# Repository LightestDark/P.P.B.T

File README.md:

# P.P.B.T

This project is a low-power smart keychain that combines E-paper display technology with NFC, designed to work with minimal energy and remain readable even when completely unpowered.

The system is split into two separate modules:

-E-Paper + NFC Keychain Board

Waveshare e paper display is used, following the websites recommended parts, using a crystal oscillator for graphics and a tiny flash memory for the images!
Used an NFC tag plugin for the coil for the NFC tag which calculates the impedance of the coil!

Added extra male pins for future endeavours if i want to add things to the board?

-Solar-Powered DC-DC Booster Board (external, detachable)

Follows a old schematic for an IKEA outdoor light, repurposed with smaller parts to make it cheaper, it uses a buckboost converter to get a steady flow from the solar panel to safely charge or power anything, in my case a strip of leds i will stick on the board case!

**This separation keeps the keychain compact, efficient, and flexible.**

**E PAPER + NFC SCHEMATIC/BOARD/MODEL:**

** SOLAR POWERED PSU **

The e-paper display shows text or graphics and keeps the image with zero power. Power is only needed when the display updates.
The NFC works passively, powered by the reader, allowing phones to scan the keychain even if the battery is empty.

To keep the main board simple and efficient, LED lighting is powered by a separate solar-powered DC-DC booster board. This board takes energy from a small solar panel and boosts it to drive LEDs around the keychain, without affecting the e-paper or NFC system.

CASE:

Pretty happy with the colour scheme and how it looks!

Main points of note:
PLA (probably)
Added tolerances for easy fitting since im hoping to use a friciton for the lid and the bottom
Added heat set insert holes
Added male header pin space for added functionality in the future
Added solar powered pcb on the underside, that will be wired to external solar panel and a led strip stuck onto the board
Added keychain hole onto the board (for coolness)

Underside:

Solar powered pcb on underside:

Under the hood:

Hopefully this is good enough to protect the board!

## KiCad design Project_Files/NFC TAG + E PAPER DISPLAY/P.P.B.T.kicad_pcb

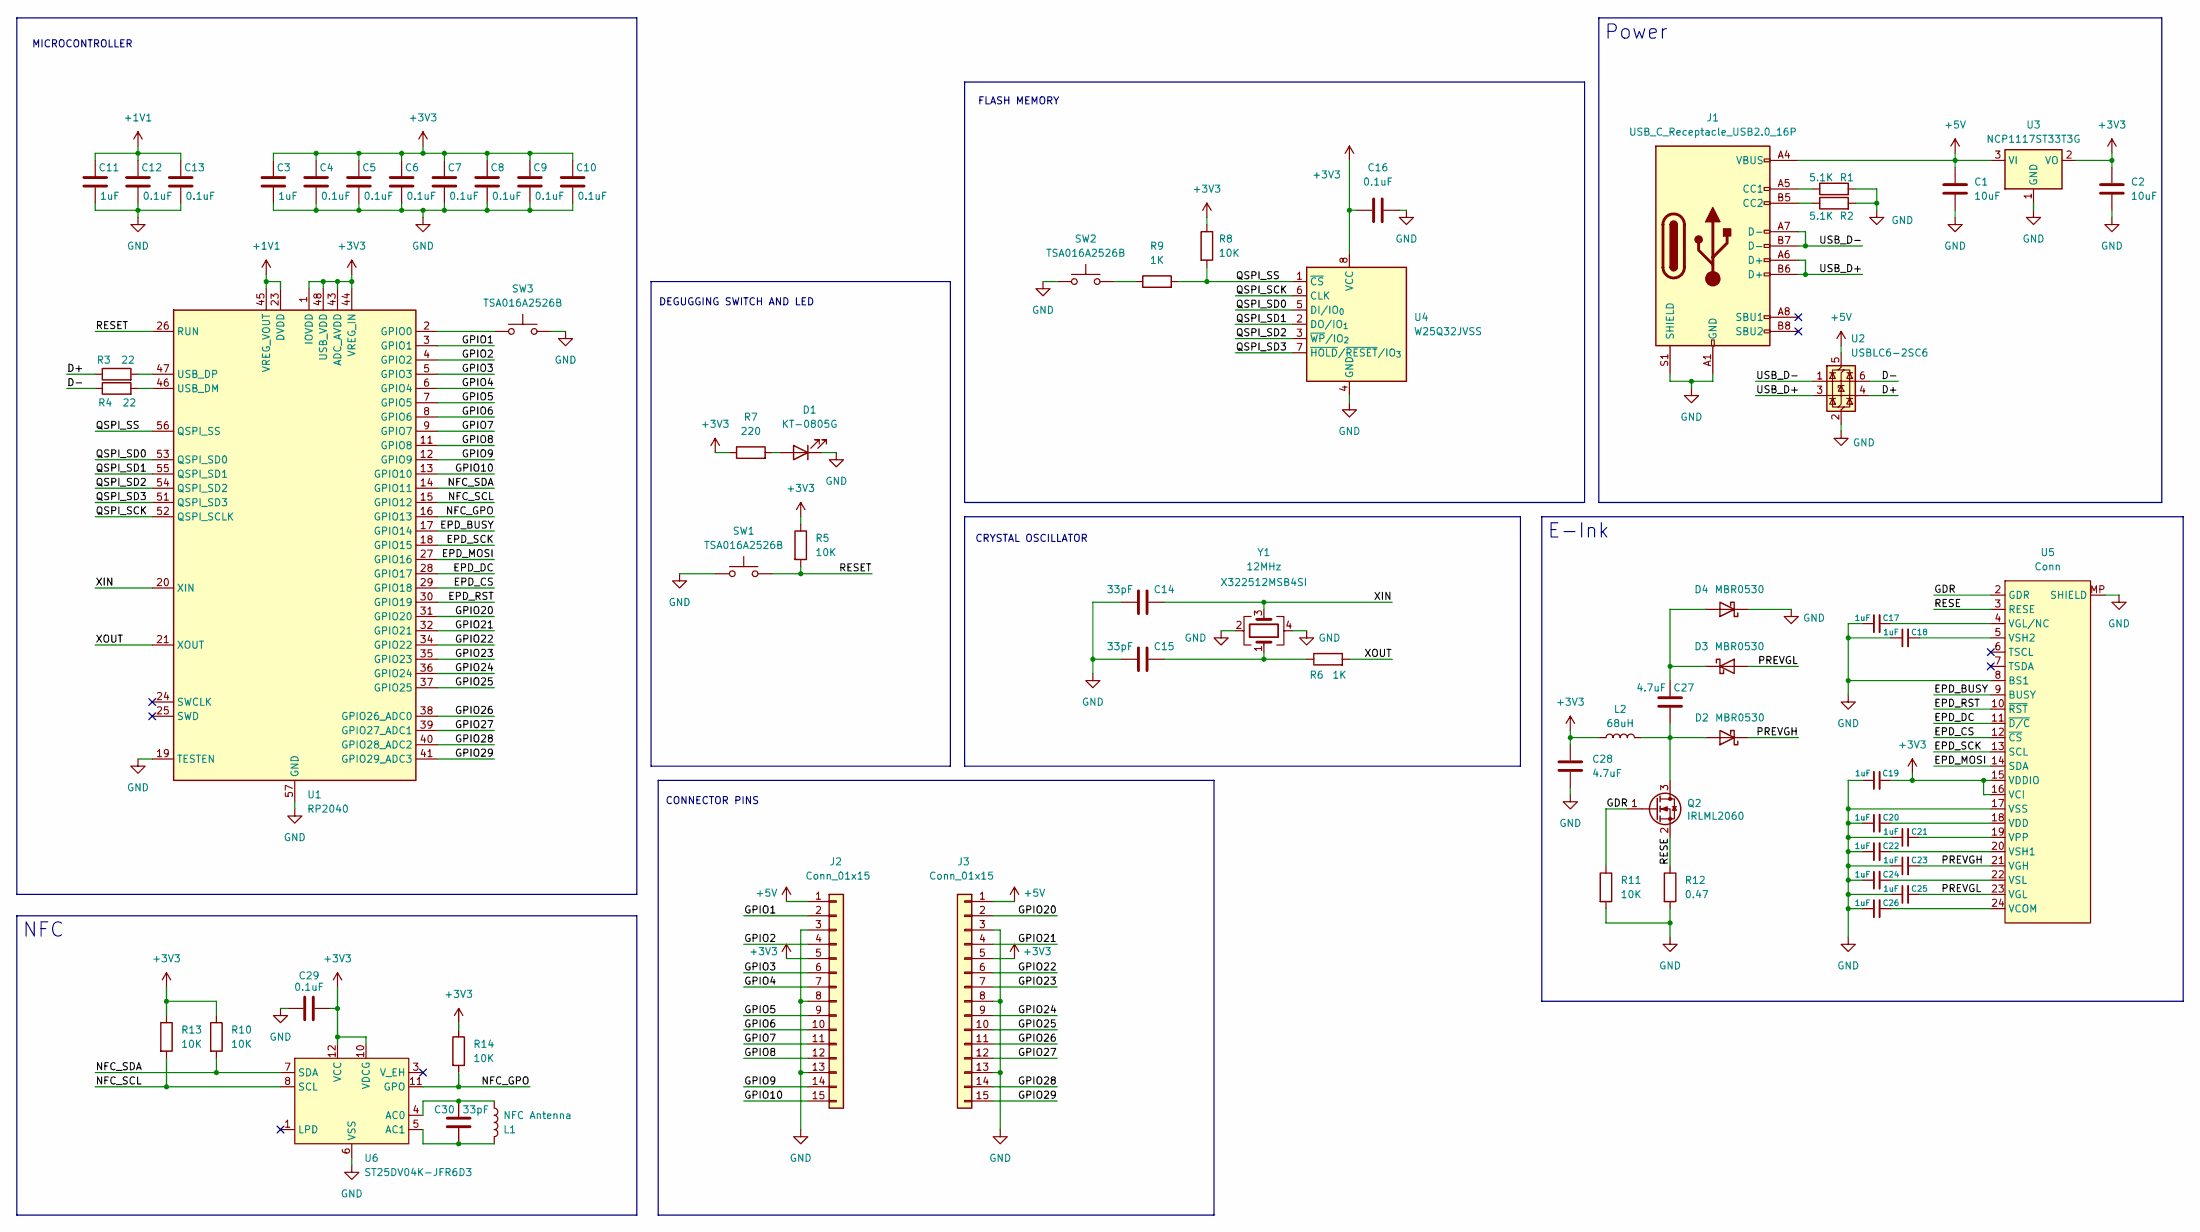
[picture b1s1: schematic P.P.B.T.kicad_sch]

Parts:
C1, C2: 10uF; C_0805_2012Metric
C3, C11, C17, C18, C19, C20, C21, C22, C23, C24, C25, C26: 1uF; C_0402_1005Metric
C4, C5, C6, C7, C8, C9, C10, C12, C13, C16, C29: 0.1uF; C_0402_1005Metric
C14, C15, C30: 33pF; C_0402_1005Metric
C27, C28: 4.7uF; C_0603_1608Metric
D1: KT-0805G; LED_0805_2012Metric
D2, D3, D4: MBR0530; D_SOD-123
J1: USB_C_Receptacle_USB2.0_16P; USB_C_Receptacle_HRO_TYPE-C-31-M-12
J2, J3: Conn_01x15; PinHeader_PAD_1x15_P2.54mm_Vertical
L1: NFC Antenna; 25x35mm-NFC
L2: 68uH; L_Changjiang_FNR6028S; MPN FNR6028S680MT
Q2: IRLML2060; SOT-23
R1, R2: 5.1K; R_0402_1005Metric
R3, R4: 22; R_0402_1005Metric
R5, R8, R10, R11, R13, R14: 10K; R_0402_1005Metric
R6, R9: 1K; R_0402_1005Metric
R7: 220; R_0402_1005Metric
R12: 0.47; R_0402_1005Metric
SW1, SW2, SW3: TSA016A2526B; SW_Push_SPST_TSA016
U1: RP2040; QFN-56-1EP_7x7mm_P0.4mm_EP3.2x3.2mm
U2: USBLC6-2SC6; SOT-23-6
U3: NCP1117ST33T3G; SOT-223-3_TabPin2
U4: W25Q32JVSS; SOIC-8_5.3x5.3mm_P1.27mm
U5: Conn; LCSC_1x24-1MP_P0.5mm_Horizontal; LCSC Part # C262567
U6: ST25DV04K-JFR6D3; ST_UFDFPN-12-1EP_3x3mm_P0.5mm_EP1.4x2.55mm
Y1: 12MHz; Crystal_SMD_3225-4Pin_3.2x2.5mm; MPN X322512MSB4SI

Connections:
+1V1: C11.1, C12.1, C13.1, U1.23 (DVDD), U1.45 (VREG_VOUT), U1.50 (DVDD)
+3V3: C2.1, C3.1, C4.1, C5.1, C6.1, C7.1, C8.1, C9.1, C10.1, C16.1, C19.2, C28.2, C29.2, J2.5, J3.5, L2.1, R5.1, R7.1, R8.1, R10.1, R13.1, R14.1, U1.1 (IOVDD), U1.10 (IOVDD), U1.22 (IOVDD), U1.33 (IOVDD), U1.42 (IOVDD), U1.43 (ADC_AVDD), U1.44 (VREG_IN), U1.48 (USB_VDD), U1.49 (IOVDD), U3.2 (VO), U4.8 (VCC), U5.15 (VDDIO), U5.16 (VCI), U6.10 (VDCG), U6.12 (VCC)
+5V: C1.1, J1.A4 (VBUS), J1.A9 (VBUS), J1.B4 (VBUS), J1.B9 (VBUS), J2.1, J3.1, U2.5 (VBUS), U3.3 (VI)
/D+: R3.1, U2.4 (I/O2)
/D-: R4.1, U2.6 (I/O1)
/EPD_BUSY: U1.17 (GPIO14), U5.9 (BUSY)
/EPD_CS: U1.29 (GPIO18), U5.12 (~CS)
/EPD_DC: U1.28 (GPIO17), U5.11 (~D/C)
/EPD_MOSI: U1.27 (GPIO16), U5.14 (SDA)
/EPD_RST: U1.30 (GPIO19), U5.10 (~RST)
/EPD_SCK: U1.18 (GPIO15), U5.13 (SCL)
/GDR: Q2.1 (G), R11.1, U5.2 (GDR)
/GPIO1: J2.2, U1.3 (GPIO1)
/GPIO2: J2.4, U1.4 (GPIO2)
/GPIO3: J2.6, U1.5 (GPIO3)
/GPIO4: J2.7, U1.6 (GPIO4)
/GPIO5: J2.9, U1.7 (GPIO5)
/GPIO6: J2.10, U1.8 (GPIO6)
/GPIO7: J2.11, U1.9 (GPIO7)
/GPIO8: J2.12, U1.11 (GPIO8)
/GPIO9: J2.14, U1.12 (GPIO9)
/GPIO10: J2.15, U1.13 (GPIO10)
/GPIO20: J3.2, U1.31 (GPIO20)
/GPIO21: J3.4, U1.32 (GPIO21)
/GPIO22: J3.6, U1.34 (GPIO22)
/GPIO23: J3.7, U1.35 (GPIO23)
/GPIO24: J3.9, U1.36 (GPIO24)
/GPIO25: J3.10, U1.37 (GPIO25)
/GPIO26: J3.11, U1.38 (GPIO26_ADC0)
/GPIO27: J3.12, U1.39 (GPIO27_ADC1)
/GPIO28: J3.14, U1.40 (GPIO28_ADC2)
/GPIO29: J3.15, U1.41 (GPIO29_ADC3)
/NFC_GPO: R14.2, U1.16 (GPIO13), U6.11 (GPO)
/NFC_SCL: R13.2, U1.15 (GPIO12), U6.8 (SCL)
/NFC_SDA: R10.2, U1.14 (GPIO11), U6.7 (SDA)
/PREVGH: C23.2, D2.1 (K), U5.21 (VGH)
/PREVGL: C25.2, D3.2 (A), U5.23 (VGL)
/QSPI_SCK: U1.52 (QSPI_SCLK), U4.6 (CLK)
/QSPI_SD0: U1.53 (QSPI_SD0), U4.5 (DI/IO_{0})
/QSPI_SD1: U1.55 (QSPI_SD1), U4.2 (DO/IO_{1})
/QSPI_SD2: U1.54 (QSPI_SD2), U4.3 (~WP/IO_{2})
/QSPI_SD3: U1.51 (QSPI_SD3), U4.7 (~HOLD/~RESET/IO_{3})
/QSPI_SS: R8.2, R9.2, U1.56 (QSPI_SS), U4.1 (~CS)
/RESE: Q2.2 (S), R12.1, U5.3 (RESE)
/RESET: R5.2, SW1.2, U1.26 (RUN)
/USB_D+: J1.A6 (D+), J1.B6 (D+), U2.3 (I/O2)
/USB_D-: J1.A7 (D-), J1.B7 (D-), U2.1 (I/O1)
/XIN: C14.2, U1.20 (XIN), Y1.3
/XOUT: R6.2, U1.21 (XOUT)
GND: C1.2, C2.2, C3.2, C4.2, C5.2, C6.2, C7.2, C8.2, C9.2, C10.2, C11.2, C12.2, C13.2, C14.1, C15.1, C16.2, C17.1, C18.1, C19.1, C20.1, C21.1, C22.1, C23.1, C24.1, C25.1, C26.1, C28.1, C29.1, D1.1 (K), D4.1 (K), J1.A1 (GND), J1.A12 (GND), J1.B1 (GND), J1.B12 (GND), J1.S1 (SHIELD), J2.3, J2.8, J2.13, J3.3, J3.8, J3.13, R1.2, R2.2, R11.2, R12.2, SW1.1, SW2.1, SW3.2, U1.19 (TESTEN), U1.57 (GND), U2.2 (GND), U3.1 (GND), U4.4 (GND), U5.8 (BS1), U5.17 (VSS), U5.MP (SHIELD), U6.6 (VSS), Y1.2, Y1.4
unnamed: C15.2, R6.1, Y1.1
unnamed: D1.2 (A), R7.2
unnamed: C27.2, D2.2 (A), L2.2, Q2.3 (D)
unnamed: C27.1, D3.1 (K), D4.2 (A)
unnamed: J1.A5 (CC1), R1.1
unnamed: J1.B5 (CC2), R2.1
unnamed: R9.1, SW2.2
unnamed: SW3.1, U1.2 (GPIO0)
unnamed: R4.2, U1.46 (USB_DM)
unnamed: R3.2, U1.47 (USB_DP)
unnamed: C26.2, U5.24 (VCOM)
unnamed: C20.2, U5.18 (VDD)
unnamed: C17.2, U5.4 (VGL/NC)
unnamed: C21.2, U5.19 (VPP)
unnamed: C22.2, U5.20 (VSH1)
unnamed: C18.2, U5.5 (VSH2)
unnamed: C24.2, U5.22 (VSL)
unnamed: C30.2, L1.2, U6.4 (AC0)
unnamed: C30.1, L1.1, U6.5 (AC1)

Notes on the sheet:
CONNECTOR PINS
FLASH MEMORY
DEGUGGING SWITCH AND LED
CRYSTAL OSCILLATOR
MICROCONTROLLER
E-Ink
Power
NFC

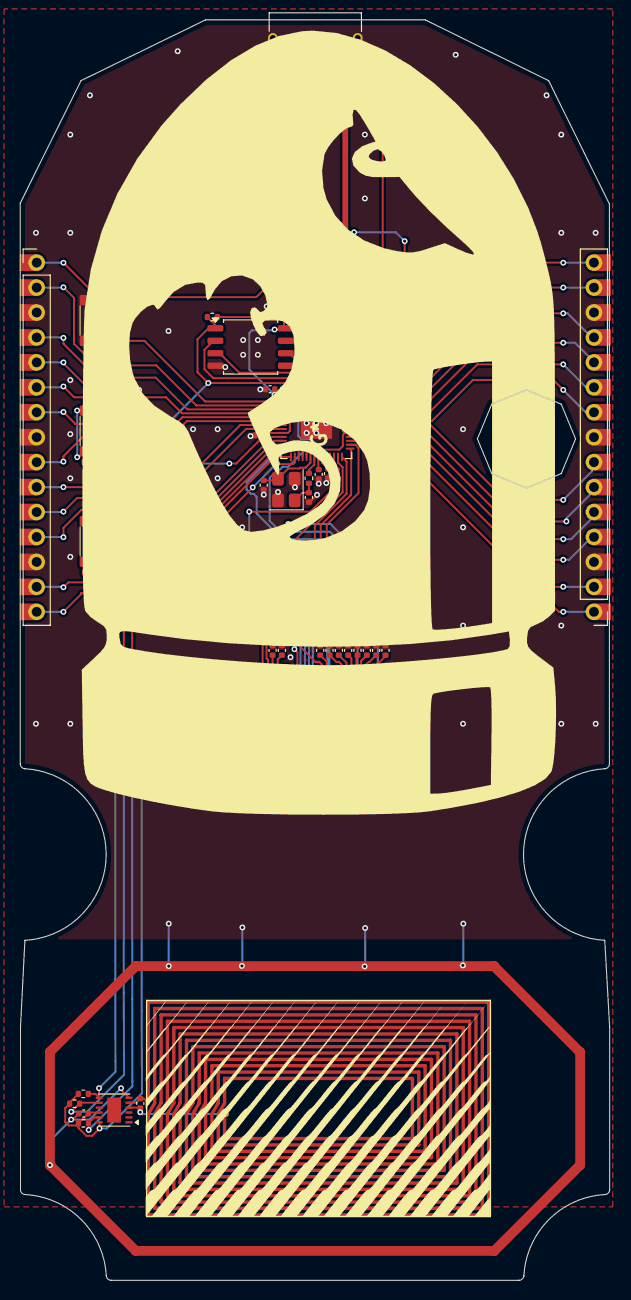
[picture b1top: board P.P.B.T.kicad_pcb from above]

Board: 2 copper layers, 60.0 x 128.4 mm, 64 parts (0 on the bottom side), 69 nets.

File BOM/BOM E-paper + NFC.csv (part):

JLCPCB BOM Tool - BOM Matching,,,,,,,,,,,,,,,,,
BOM name：bom-JLCPCB Assembly Order.xlsx,,,Download Time：2025-12-15 06:33:50,,,,"* Our matching results are updated in real-time, but stock and prices may change. 
If it's been over 24 hours, please re-match before placing your order.",,,,,,,,,,
PCB Assembled Qty：5,,,Est. Total Price：15.1631,,,,,,,,,,,,,,
Your BOM,,,,,Matched Parts,,,,,,,Order Information,,,,,
Top Designator,Bottom Designator,Comment,Footprint,JLCPCB Part #,Matches,Part # ,Manufacturer,Footprint,Description,Category,Warning,JLCPCB Part #,Product link,Lib Type,Qty,Source,Total Price ($)
"C1,C2",,10uF,0805,,Select by System,CL21A106KAYNNNE,Samsung Electro-Mechanics,0805,10uF 25V X5R ±10% 0805 Multilayer Ceramic Capacitors MLCC - SMD/SMT ROHS,Multilayer Ceramic Capacitors MLCC - SMD/SMT,,C15850,https://jlcpcb.com/partdetail/16532-CL21A106KAYNNNE/C15850,Basic,10,10 JLCPCB,0.098
"C10,C12,C13,C16,C29,C4,C5,C6,C7,C8,C9",,0.1uF,0402,,Unconfirmed,CL05B104KO5NNNC,Samsung Electro-Mechanics,0402,100nF 16V X7R ±10% 0402 Multilayer Ceramic Capacitors MLCC - SMD/SMT ROHS,Multilayer Ceramic Capacitors MLCC - SMD/SMT,1.The comment (CL05B104KO5NNNC) of this part does not match the one (0.1uF) provided in your BOM. Please confirm;,C1525,https://jlcpcb.com/partdetail/1877-CL05B104KO5NNNC/C1525,Basic,55,55 JLCPCB,0.066
"C11,C17,C18,C19,C20,C21,C22,C23,C24,C25,C26,C3",,1uF,0402,,Select by System,CL05A105KA5NQNC,Samsung Electro-Mechanics,0402,1uF 25V X5R ±10% 0402 Multilayer Ceramic Capacitors MLCC - SMD/SMT ROHS,Multilayer Ceramic Capacitors MLCC - SMD/SMT,,C52923,https://jlcpcb.com/partdetail/53938-CL05A105KA5NQNC/C52923,Basic,60,60 JLCPCB,0.174
"C14,C15,C30",,33pF,0402,,Select by System,0402CG330J500NT,FH (Guangdong Fenghua Advanced Tech),0402,33pF 50V C0G ±5% 0402 Multilayer Ceramic Capacitors MLCC - SMD/SMT ROHS,Multilayer Ceramic Capacitors MLCC - SMD/SMT,,C1562,https://jlcpcb.com/partdetail/1914-0402CG330J500NT/C1562,Basic,15,15 JLCPCB,0.015
"C27,C28",,4.7uF,0603,,Select by System,CL10A475KO8NNNC,Samsung Electro-Mechanics,0603,16V 4.7uF X5R ±10% 0603 Multilayer Ceramic Capacitors MLCC - SMD/SMT ROHS,Multilayer Ceramic Capacitors MLCC - SMD/SMT,,C19666,https://jlcpcb.com/partdetail/20375-CL10A475KO8NNNC/C19666,Basic,10,10 JLCPCB,0.092
D1,,KT-0805G,0805,,Select by System,KT-0805G,Hubei KENTO Elec,0805,-40℃~+85℃ 100mW 120° 2.6V~3.1V 430mcd 513nm~528nm 525nm 5mA Emerald Green 0805 LED Indication - Discrete ROHS,LED Indication - Discrete,,C2297,https://jlcpcb.com/partdetail/Hubei_KENTOElec-KT0805G/C2297,Basic,5,5 JLCPCB,0.054
"D2,D3,D4",,MBR0530,D_SOD-123,,Select by System,MBR0530,TWGMC,SOD-123,130uA 30V 5.5A 500mA 500mV@500mA Independent SOD-123 Schottky Diodes ROHS,Schottky Diodes,,C5204746,https://jlcpcb.com/partdetail/TWGMC-MBR0530/C5204746,Extended,23,23 JLCPCB,0.4278
J1,,USB_C_Receptacle_USB2.0_16P,USB_C_Receptacle_HRO_TYPE-C-31-M-12,,Select by Customer,TYPE-C-31-M-12,Korean Hroparts Elec,SMD,1 16P 5A Female Type-C SMD USB Connectors ROHS,USB Connectors,,C165948,https://jlcpcb.com/partdetail/Korean_HropartsElec-TYPE_C_31_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,Extended,5,5 JLCPCB,0.847
L2,,68uH,L_Changjiang_FNR6028S,,Select by Customer,FNR6028S680MT,cjiang (Changjiang Microelectronics Tech),"SMD,6x6mm","468mΩ 68uH 950mA 950mA Magnetic Shielded Inductor ±20% SMD,6x6mm Power Inductors ROHS",Power Inductors,,C168045,https://jlcpcb.com/partdetail/179428-FNR6028S680MT/C168045,Extended,6,6 JLCPCB,0.3978
Q2,,IRLML2060,SOT-23,,Unconfirmed,IRLML2060TRPBF,TECH PUBLIC,SOT-23,105mΩ@10V 19.5pF 247pF 2V 34pF 350mW 3A 60V 6nC@4.5V SOT-23 MOSFETs ROHS,MOSFETs,1.The comment (IRLML2060TRPBF) of this part does not match the one (IRLML2060) provided in your BOM. Please confirm;,C5122027,https://jlcpcb.com/partdetail/TECHPUBLIC-IRLML2060TRPBF/C5122027,Extended,9,9 JLCPCB,0.5607
"R1,R2",,5.1K,0402,,Unconfirmed,0402WGF5101TCE,UNI-ROYAL(Uniroyal Elec),0402,-55℃~+155℃ 5.1kΩ 50V 62.5mW Thick Film Resistor ±1% ±100ppm/℃ 0402 Chip Resistor - Surface Mount ROHS,Chip Resistor - Surface Mount,1.The comment (0402WGF5101TCE) of this part does not match the one (5.1K) provided in your BOM. Please confirm;,C25905,https://jlcpcb.com/partdetail/26648-0402WGF5101TCE/C25905,Basic,10,10 JLCPCB,0.005
"R3,R4",,22,0402,,Unconfirmed,0402WGF220JTCE,UNI-ROYAL(Uniroyal Elec),0402,-55℃~+155℃ 22Ω 50V 62.5mW Thick Film Resistor ±1% ±100ppm/℃ 0402 Chip Resistor - Surface Mount ROHS,Chip Resistor - Surface Mount,1.The comment (0402WGF220JTCE) of this part does not match the one (22) provided in your BOM. Please confirm;,C25092,https://jlcpcb.com/partdetail/25835-0402WGF220JTCE/C25092,Basic,10,10 JLCPCB,0.006
"R6,R9",,1K,0402,,Unconfirmed,0402WGF1001TCE,UNI-ROYAL(Uniroyal Elec),0402,-55℃~+155℃ 1kΩ 50V 62.5mW Thick Film Resistor ±1% ±100ppm/℃ 0402 Chip Resistor - Surface Mount ROHS,Chip Resistor - Surface Mount,1.The comment (0402WGF1001TCE) of this part does not match the one (1K) provided in your BOM. Please confirm;,C11702,https://jlcpcb.com/partdetail/12256-0402WGF1001TCE/C11702,Basic,10,10 JLCPCB,0.006
R7,,220,0402,,Unconfirmed,0402WGF2200TCE,UNI-ROYAL(Uniroyal Elec),0402,-55℃~+155℃ 220Ω 50V 62.5mW Thick Film Resistor ±1% ±100ppm/℃ 0402 Chip Resistor - Surface Mount ROHS,Chip Resistor - Surface Mount,1.The comment (0402WGF2200TCE) of this part does not match the one (220) provided in your BOM. Please confirm;,C25091,https://jlcpcb.com/partdetail/25834-0402WGF2200TCE/C25091,Basic,5,5 JLCPCB,0.003
"R10,R11,R13,R14,R5,R8",,10K,0402,,Unconfirmed,0402WGF1002TCE,UNI-ROYAL(Uniroyal Elec),0402,-55℃~+155℃ 10kΩ 50V 62.5mW Thick Film Resistor ±1% ±100ppm/℃ 0402 Chip Resistor - Surface Mount ROHS,Chip Resistor - Surface Mount,1.The comment (0402WGF1002TCE) of this part does not match the one (10K) provided in your BOM. Please confirm;,C25744,https://jlcpcb.com/partdetail/26487-0402WGF1002TCE/C25744,Basic,30,30 JLCPCB,0.015
R12,,0.47,0402,,Unconfirmed,0402WGF470LTCE,UNI-ROYAL(Uniroyal Elec),0402,-55℃~+155℃ 470mΩ 50V 62.5mW Thick Film Resistor ±1% ±800ppm/℃ 0402 Chip Resistor - Surface Mount ROHS,Chip Resistor - Surface Mount,1.The comment (0402WGF470LTCE) of this part does not match the one (0.47) provided in your BOM. Please confirm;,C423162,https://jlcpcb.com/partdetail/416112-0402WGF470LTCE/C423162,Extended,20,20 JLCPCB,0.078
"SW1,SW2,SW3",,TSA016A2526B,SW_Push_SPST_TSA016,,Select by System,TSA016A2526B,BZCN,"SMD,4.2x3.4mm","12V 2.5mm 2.6N 3.35mm 4.2mm 50mA Oval Button Surface Mount,Vertical White SMD,4.2x3.4mm Tactile Switches ROHS",Tactile Switches,,C2888429,https://jlcpcb.com/partdetail/BZCN-TSA016A2526B/C2888429,Extended,20,20 JLCPCB,0.418
U1,,RP2040,QFN-56-1EP_7x7mm_P0.4mm_EP3.2x3.2mm,,Select by Customer,RP2040,Raspberry Pi,LQFN-56(7x7),12bit 133MHz 30 LQFN-56(7x7) Microcontrollers (MCU/MPU/SOC) ROHS,Microcontrollers (MCU/MPU/SOC),,C2040,https://jlcpcb.com/partdetail/RaspberryPi-RP2040/C2040,Extended,5,5 JLCPCB,4.5825
U2,,USBLC6-2SC6,SOT-23-6,,Select by System,USBLC6-2SC6,TECH PUBLIC,SOT-23-6,-55℃~+125℃ 0.35pF 12V 150W 2 5V 6A 6V 80nA ESD IEC 61000-4-2 Unidirectional SOT-23-6 ESD and Surge Protection (TVS/ESD) ROHS,ESD And Surge Protection (TVS/ESD),,C2827654,https://jlcpcb.com/partdetail/TECHPUBLIC-USBLC62SC6/C2827654,Extended,9,9 JLCPCB,0.3348
U3,,NCP1117ST33T3G,SOT-223-3_TabPin2,,Select by System,NCP1117ST33T3G,onsemi,SOT-223,"0.003%Vout 0℃~+125℃@(Ta) 1 1.2V@(800mA) 1A 20V 3.3V 62dB@(120Hz) 6mA Fixed Over Current Protection Positive SOT-223 Voltage Regulators - Linear, Low Drop Out (LDO) Regulators ROHS","Voltage Regulators - Linear, Low Drop Out (LDO) Regulators",,C26537,https://jlcpcb.com/partdetail/onsemi-NCP1117ST33T3G/C26537,Extended,5,5 JLCPCB,1.119
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
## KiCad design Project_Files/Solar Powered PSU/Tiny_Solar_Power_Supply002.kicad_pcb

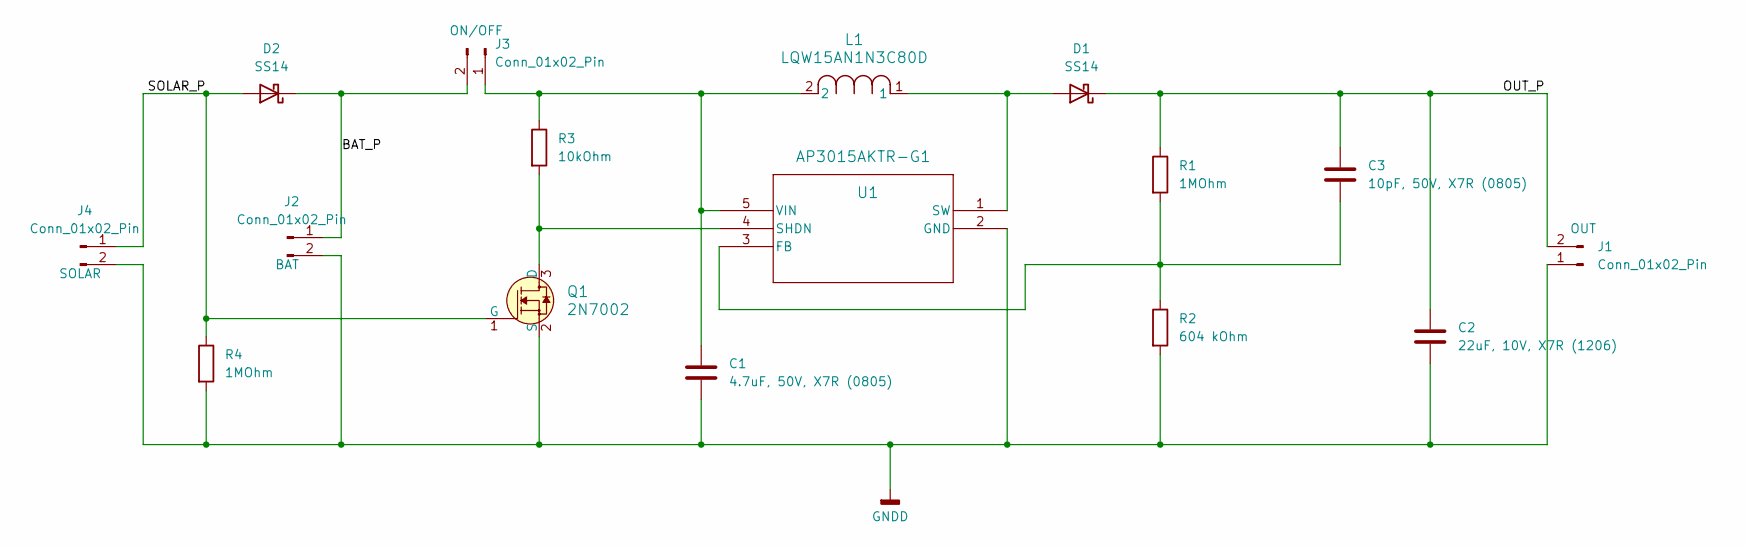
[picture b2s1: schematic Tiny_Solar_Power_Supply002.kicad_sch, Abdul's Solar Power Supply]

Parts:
C1: 4.7uF, 50V, X7R (0805); C_0805_2012Metric
C2: 22uF, 10V, X7R (1206); C_1206_3216Metric
C3: 10pF, 50V, X7R (0805); C_0805_2012Metric
D1, D2: SS14; D_SMA
J1, J2, J3: Conn_01x02_Pin; PinHeader_1x02_P2.54mm_Vertical
J4: Conn_01x02_Pin; PinHeader_1x02_P2.54mm_Horizontal
L1: LQW15AN1N3C80D; IND_LQW15_MUR
Q1: 2N7002; SOT-23-3; MPN 2N7002; Digi-Key_PN 2N7002NCT-ND
R1, R4: 1MOhm; R_0805_2012Metric
R2: 604 kOhm; R_0805_2012Metric
R3: 10kOhm; R_0805_2012Metric
U1: AP3015AKTR-G1; SOT23-5_1P55X2P9_DIO

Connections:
/BAT_P: D2.1 (K), J2.1, J3.2
/OUT_P: C2.1, C3.1, D1.1 (K), J1.2, R1.1
/SOLAR_P: D2.2 (A), J4.1, Q1.1 (G), R4.1
GNDD: C1.2, C2.2, J1.1, J2.2, J4.2, Q1.2 (S), R2.2, R4.2, U1.2 (GND)
unnamed: D1.2 (A), L1.1, U1.1 (SW)
unnamed: C1.1, J3.1, L1.2, R3.1, U1.5 (VIN)
unnamed: Q1.3 (D), R3.2, U1.4 (SHDN)
unnamed: C3.2, R1.2, R2.1, U1.3 (FB)

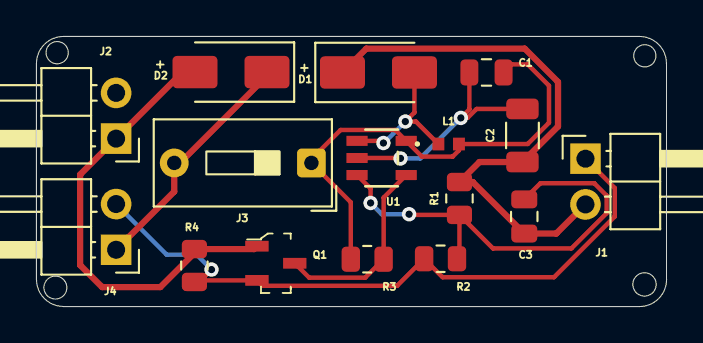
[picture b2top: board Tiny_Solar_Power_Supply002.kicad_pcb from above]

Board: 2 copper layers, 35.0 x 15.0 mm, 16 parts (0 on the bottom side), 8 nets.

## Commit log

2026-01-10 Create a
2026-01-10 Add files via upload
    BOM AND POSITION FILES
2026-01-10 Create E-Paper + NFC
2026-01-10 Create Solar Panel PSU
2026-01-10 Rename Solar Panel PSU to Solar Panel PSU.csv
